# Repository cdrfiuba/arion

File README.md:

# Arión

Arión es un seguidor de líneas basado en la categoría Micromouse. Se caracteriza por ser tanto pequeño como liviano, y por estar siempre en búsqueda de innovaciones que le permitan tener mayor velocidad y mejor control, mediante diferentes mejoras de mecánica, electrónica y software. Nuestro objetivo es ganar las varias competencias de carreras que organiza la Liga Nacional de Robótica, mientras proporcionamos un diseño abierto y fácilmente replicable, para que cualquiera pueda hacer su propio robot y hacerle las modificaciones que potencien el estado de la robótica en nuestro país.

## Estado Actual

Un primer prototipo con varias adaptaciones obtuvo el tercer lugar en la Liga Nacional de Robótica de 2015. Actualmente estamos estandarizando estas adaptaciones para tener un diseño monolítico, tanto de mecánica y electrónica como de software.

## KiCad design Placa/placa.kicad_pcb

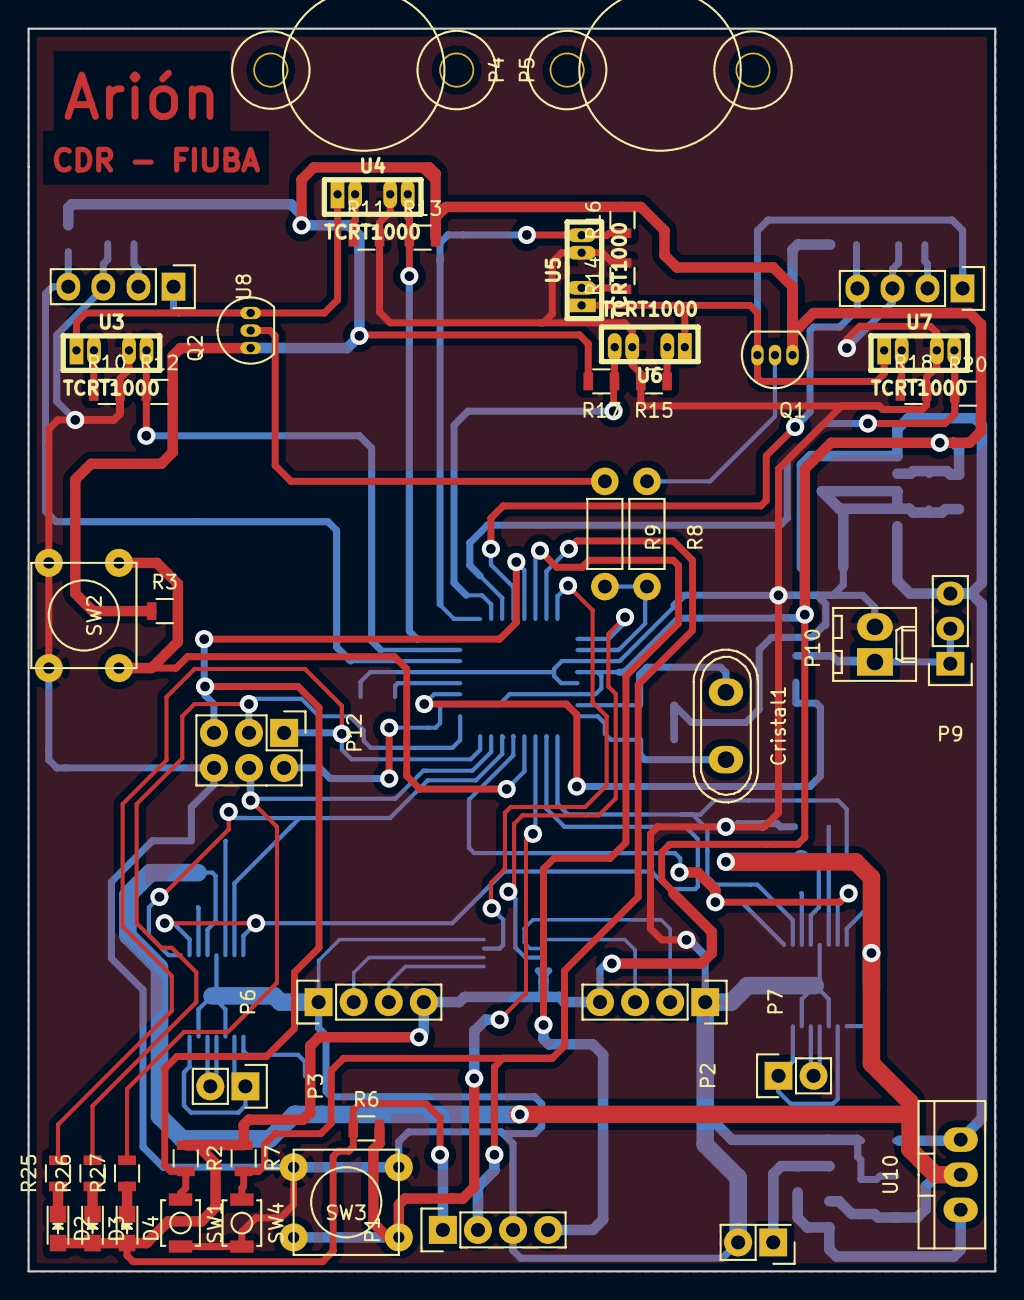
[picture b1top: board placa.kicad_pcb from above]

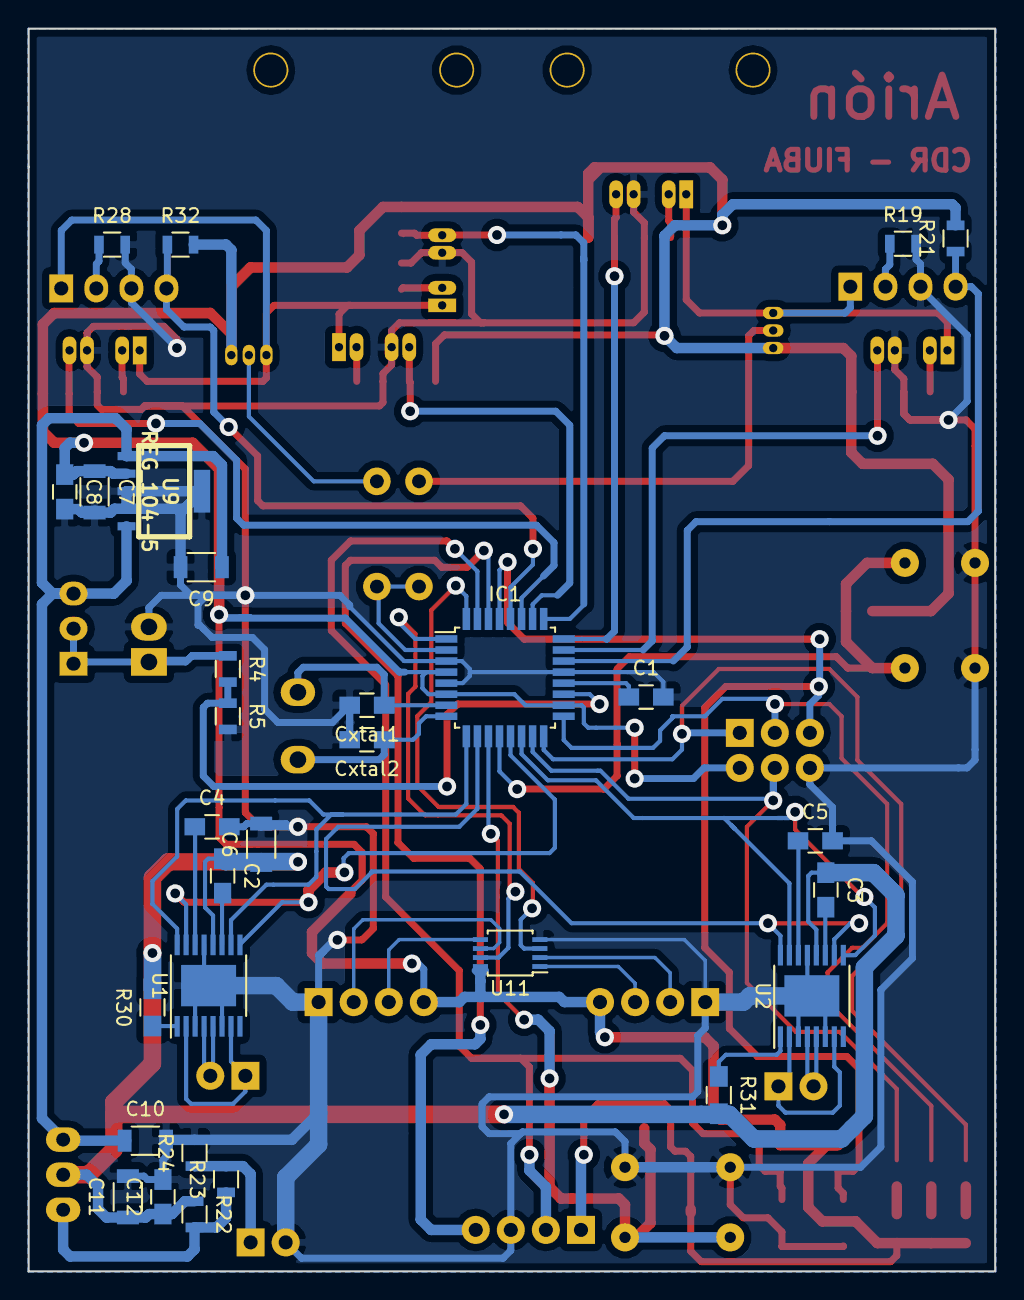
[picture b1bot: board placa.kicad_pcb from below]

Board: 2 copper layers, 70.0 x 90.0 mm, 78 parts (30 on the bottom side), 61 nets.

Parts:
C1: C; C_0805_HandSoldering
C2, C3: 0.01u; C_0805_HandSoldering
C4, C5: 2.2u; C_0805_HandSoldering
C6: 10uF; C_1206
C7, C9, C10, C11: 10u; C_1206
C8: 100n; C_0805_HandSoldering
C12: 0.1u; C_0805_HandSoldering
Cristal1: Crystal; Crystal_HC50-U_Vertical
Cxtal1, Cxtal2: 22p; C_0805_HandSoldering
D2, D3, D4: LED; LED_0805
IC1: ATMEGA328-A; TQFP-32_7x7mm_Pitch0.8mm
JP1: JUMPER; Pin_Header_Straight_2x01
P1, P6, P7: CONN_01X04; Pin_Header_Straight_1x04
P2, P3: CONN_01X02; Pin_Header_Straight_1x02
P4: BallCaster2; Pin_Header_Straight_1x02
P5: BallCaster1; Pin_Header_Straight_1x02
P9: CONN_01X03; Pin_Header_Straight_1x03
P10: CONN_01X02; Molex_KK-6410-02_02x2.54mm_Straight
P12: CONN_02X03; Pin_Header_Straight_2x03
Q1, Q2: BC548; TO-92_Inline_Narrow_Oval
R2, R3, R6, R7: 10k; R_0805
R4, R5, R12, R13, R16, R17, R20, R21, R32: 33k; R_0805
R8, R9: 2k2; Resistor_Horizontal_RM7mm
R10, R11, R14, R15, R18, R19, R28: 180; R_0805
R22: 120; R_0805
R23: 470; R_0805
R24: 270; R_0805
R25, R26, R27: 220; R_0805
R30, R31: 47k; R_0805_HandSoldering
SW1, SW4: SW_PUSH_SMALL; SW_SPST_B3U-1000P
SW2, SW3: SW_PUSH_SMALL
U1, U2: DVR8833; TSSOP-16_4.4x5mm_Pitch0.65mm
U3, U4, U5, U6, U7: TCRT1000
U8, U12: TCRT1000; Pin_Header_Straight_1x04
U9: REG_104-5; SOT223-5
U10: LM1084IT-ADJ/NOPB; TO-220_Neutral123_Vertical
U11: sn74lvc2g86; TSSOP-8_3x3mm_Pitch0.65mm

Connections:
+5V: C7.1, C8.1, D2.2, D3.2, D4.2, IC1.4, IC1.6, IC1.18, P1.1, P6.4, P7.4, P12.2, Q1.1, Q2.1, R2.1, R3.1, R6.1, R7.1, R12.2, R13.2, R16.2, R17.2, R20.2, R21.2, R32.2, U9.2, U11.8
+BATT: P9.1, P9.2, P10.1, R4.1
/Alimentacion/Vbat: C9.1, C10.1, P9.3, U9.1, U9.5, U10.3
/BatteryControl: IC1.19, R4.2, R5.1
/Boton1: IC1.12, R3.2, SW2.1
/Boton2: IC1.11, R6.2, SW3.1
/BotonExtra: IC1.31, P1.2, R7.2, SW4.1
/EncoderM1: IC1.1, U11.7
/EncoderM2: IC1.32, U11.3
/Led1: IC1.15, P12.4, R27.2
/Led2: IC1.16, P12.1, R25.2
/Led3: IC1.17, P12.3, R26.2
/Motores/M1IN1: IC1.13, U1.9, U1.15
/Motores/M1IN2: IC1.9, U1.10, U1.16
/Motores/M1OUT1: P2.1, U1.2, U1.7
/Motores/M1OUT2: P2.2, U1.4, U1.5
/Motores/M1VCP: C2.2, U1.11
/Motores/M1VINT: C4.1, U1.14
/Motores/M2IN1: IC1.14, U2.9, U2.15
/Motores/M2IN2: IC1.10, U2.10, U2.16
/Motores/M2OUT1: P3.1, U2.2, U2.7
/Motores/M2OUT2: P3.2, U2.4, U2.5
/Motores/M2VCP: C3.2, U2.11
/Motores/M2VINT: C5.1, U2.14
/RX: IC1.30, P1.4
/Reset: IC1.29, P12.5, R2.2, SW1.1
/Sensores/Habilitador: IC1.2, R8.2, R9.2
/Sensores/Sensor1: IC1.22, R21.1, U8.4
/Sensores/Sensor2: IC1.23, R12.1, U3.4
/Sensores/Sensor3: IC1.24, R13.1, U4.4
/Sensores/Sensor4: IC1.25, R16.1, U5.4
/Sensores/Sensor5: IC1.26, R17.1, U6.4
/Sensores/Sensor6: IC1.27, R20.1, U7.4
/Sensores/Sensor7: IC1.28, R32.1, U12.4
/Sensores/habilitado: Q1.3, U5.1, U6.1, U7.1, U12.1
/Sensores/habilitado2: Q2.3, U3.1, U4.1, U8.1
/XTAL1: Cristal1.1, Cxtal1.1, IC1.7
/XTAL2: Cristal1.2, Cxtal2.1, IC1.8
GND: C1.2, C4.2, C5.2, C6.2, C7.2, C8.2, C9.2, C10.2, C11.2, C12.2, Cxtal1.2, Cxtal2.2, IC1.3, IC1.5, IC1.21, JP1.2, P1.3, P6.1, P7.1, P10.2, P12.6, R5.2, R10.2, R11.2, R14.2, R15.2, R18.2, R19.2, R24.2, R28.2, SW1.2, SW2.2, SW3.2, SW4.2, U1.3, U1.6, U1.13, U2.3, U2.6, U2.13, U3.3, U4.3, U5.3, U6.3, U7.3, U8.3, U9.3, U9.4, U11.4, U12.3
unnamed: C1.1, IC1.20
unnamed: D2.1, R25.1
unnamed: D3.1, R26.1
unnamed: D4.1, R27.1
unnamed: JP1.1, R23.2, R24.1
unnamed: P6.2, U11.2
unnamed: P6.3, U11.1
unnamed: P7.2, U11.6
unnamed: P7.3, U11.5
unnamed: Q1.2, R8.1
unnamed: Q2.2, R9.1
unnamed: R10.1, U3.2
unnamed: R11.1, U4.2
unnamed: R14.1, U5.2
unnamed: R15.1, U6.2
unnamed: R18.1, U7.2
unnamed: R19.1, U8.2
unnamed: R22.2, R23.1, U10.1
unnamed: R28.1, U12.2
unnamed: R30.1, U1.1
unnamed: R31.1, U2.1
VPP: C2.1, C3.1, C6.1, C11.1, C12.1, R22.1, R30.2, R31.2, U1.12, U2.12, U10.2

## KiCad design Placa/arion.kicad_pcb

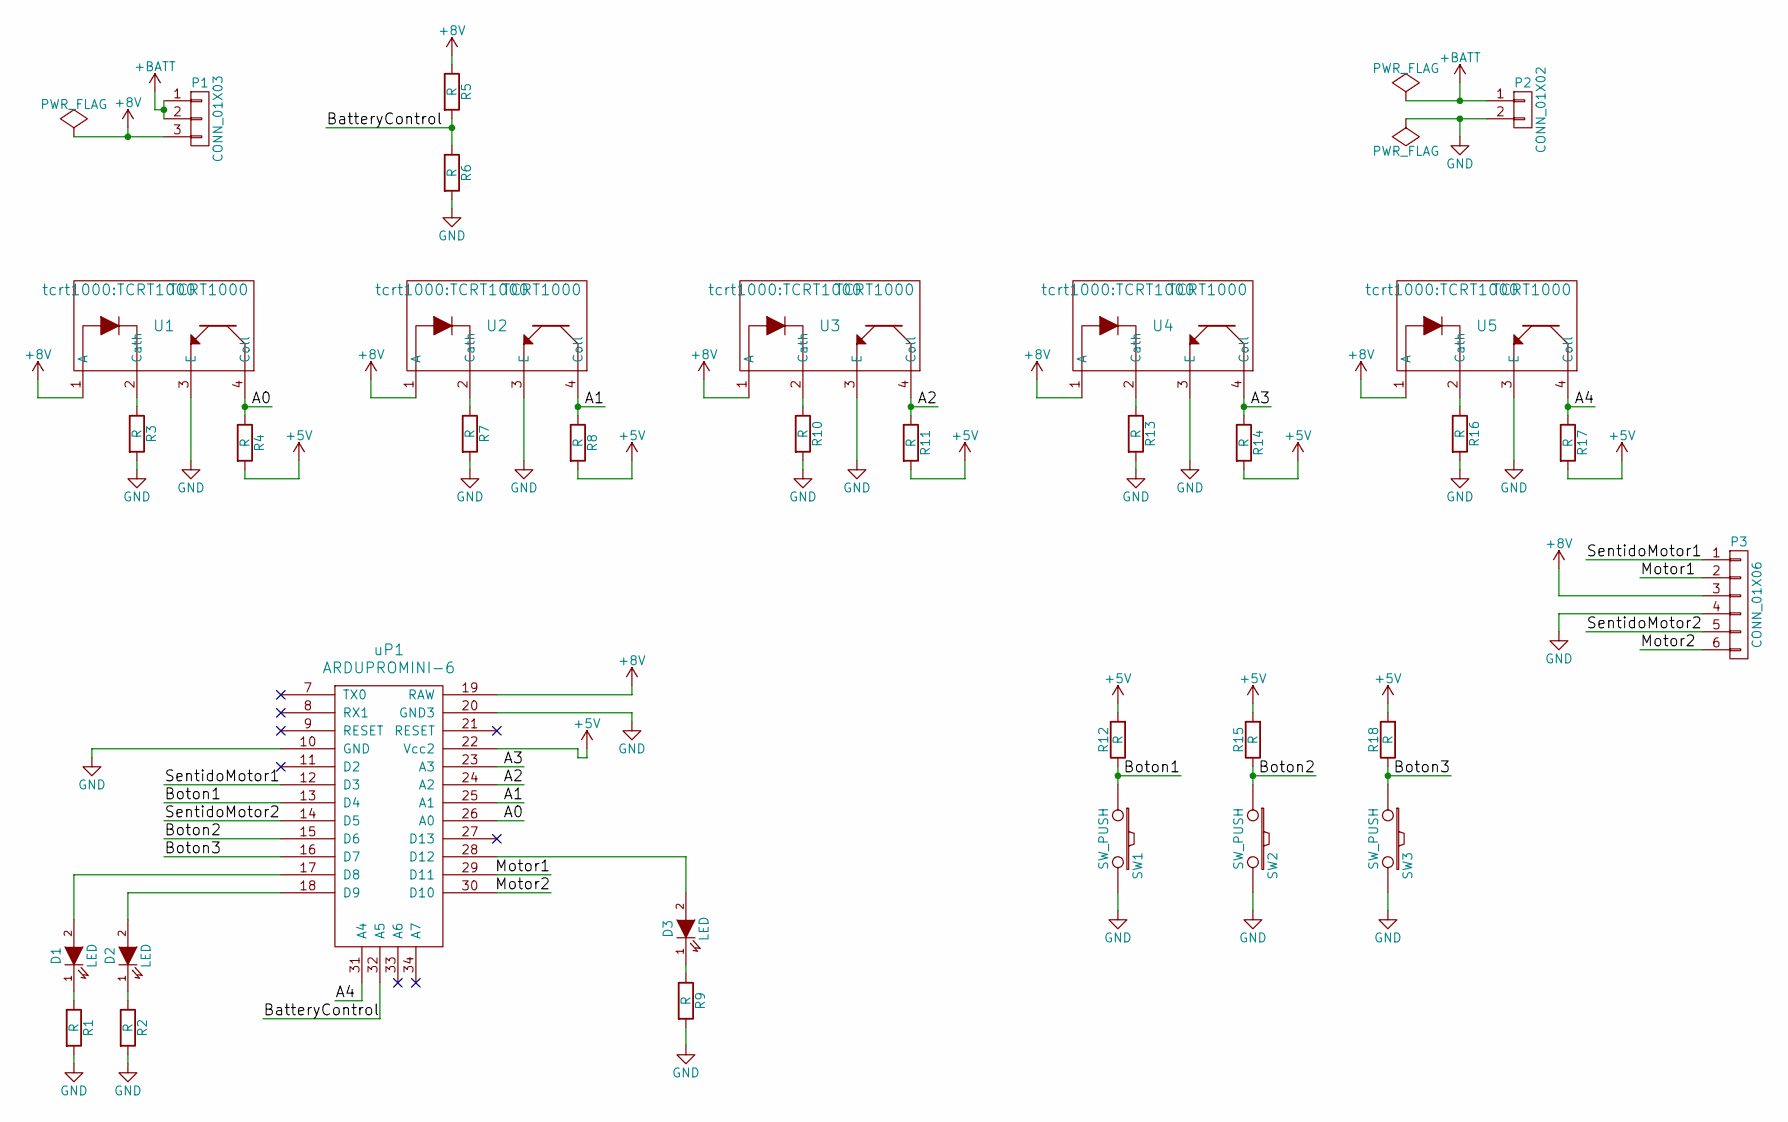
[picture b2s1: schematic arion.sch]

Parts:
D1, D2, D3: LED; R_0805_HandSoldering
P1: CONN_01X03; Pin_Header_Straight_1x03
P2: CONN_01X02; Pin_Header_Straight_1x02
P3: CONN_01X06; Pin_Header_Straight_1x06
R1, R2, R3, R4, R5, R6, R7, R8, R9, R10, R11, R12, R13, R14, R15, R16, R17, R18: R; R_0805_HandSoldering
SW1, SW2, SW3: SW_PUSH; SW_PUSH_SMALL
U1, U2, U3, U4, U5: TCRT1000
uP1: ARDUPROMINI-6; ArduProMini-6

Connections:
+5V: R4.2, R8.2, R11.2, R12.2, R14.2, R15.2, R17.2, R18.2, uP1.22 (Vcc2)
+8V: P1.3, P3.3, R5.1, U1.1 (A), U2.1 (A), U3.1 (A), U4.1 (A), U5.1 (A), uP1.19 (RAW)
+BATT: P1.1, P1.2, P2.1
/A0: R4.1, U1.4 (Coll), uP1.26 (A0)
/A1: R8.1, U2.4 (Coll), uP1.25 (A1)
/A2: R11.1, U3.4 (Coll), uP1.24 (A2)
/A3: R14.1, U4.4 (Coll), uP1.23 (A3)
/A4: R17.1, U5.4 (Coll), uP1.31 (A4)
/BatteryControl: R5.2, R6.1, uP1.32 (A5)
/Boton1: R12.1, SW1.1, uP1.13 (D4)
/Boton2: R15.1, SW2.1, uP1.15 (D6)
/Boton3: R18.1, SW3.1, uP1.16 (D7)
/Motor1: P3.2, uP1.29 (D11)
/Motor2: P3.6, uP1.30 (D10)
/SentidoMotor1: P3.1, uP1.12 (D3)
/SentidoMotor2: P3.5, uP1.14 (D5)
GND: P2.2, P3.4, R1.2, R2.2, R3.2, R6.2, R7.2, R9.2, R10.2, R13.2, R16.2, SW1.2, SW2.2, SW3.2, U1.3 (E), U2.3 (E), U3.3 (E), U4.3 (E), U5.3 (E), uP1.10 (GND), uP1.20 (GND3)
unnamed: D1.1 (K), R1.1
unnamed: D1.2 (A), uP1.17 (D8)
unnamed: D2.1 (K), R2.1
unnamed: D2.2 (A), uP1.18 (D9)
unnamed: D3.1 (K), R9.1
unnamed: D3.2 (A), uP1.28 (D12)
unnamed: R3.1, U1.2 (Cath)
unnamed: R7.1, U2.2 (Cath)
unnamed: R10.1, U3.2 (Cath)
unnamed: R13.1, U4.2 (Cath)
unnamed: R16.1, U5.2 (Cath)

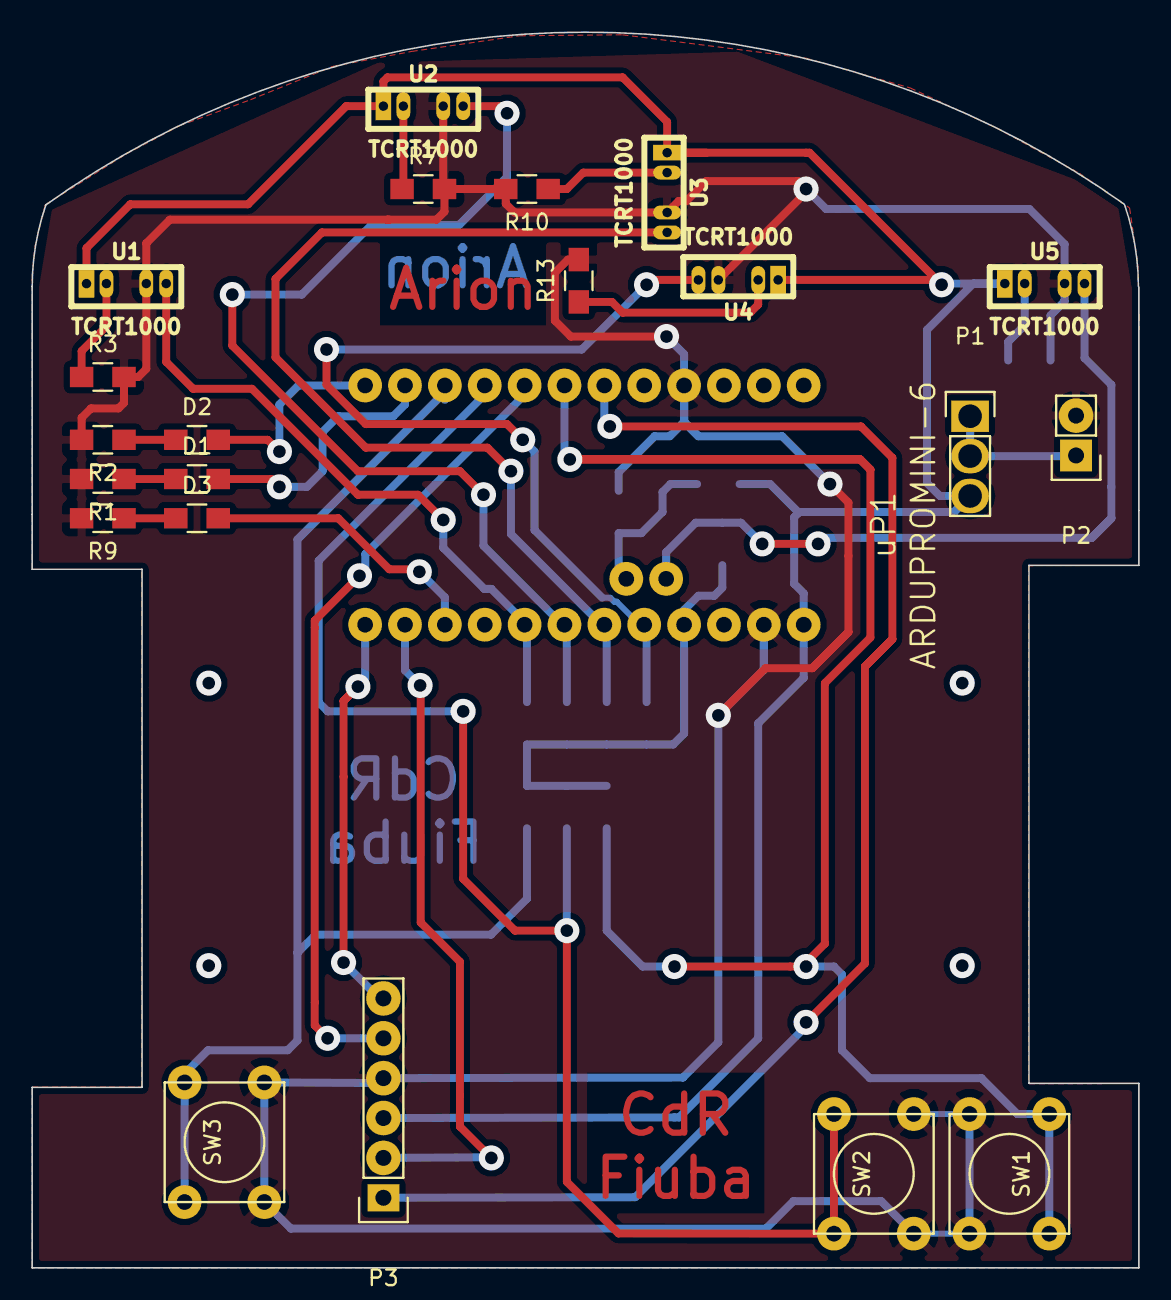
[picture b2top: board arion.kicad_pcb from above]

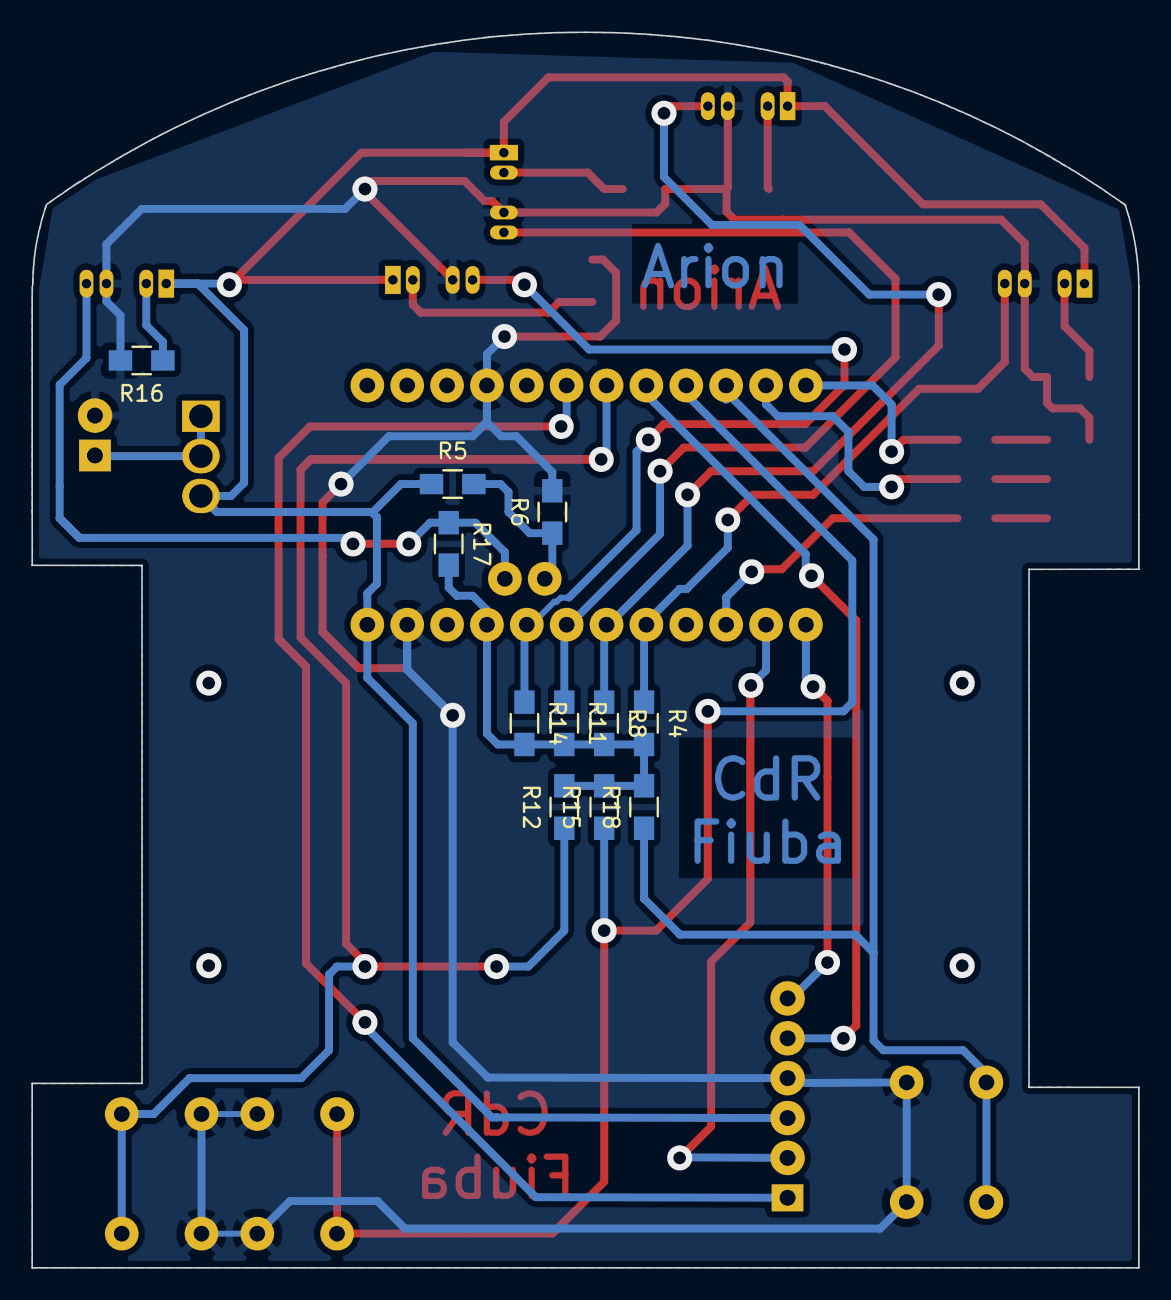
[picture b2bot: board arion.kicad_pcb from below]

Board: 2 copper layers, 70.5 x 78.7 mm, 33 parts (11 on the bottom side), 28 nets.

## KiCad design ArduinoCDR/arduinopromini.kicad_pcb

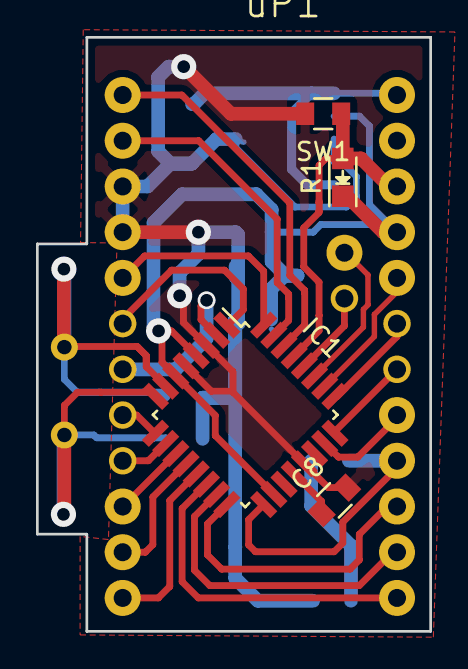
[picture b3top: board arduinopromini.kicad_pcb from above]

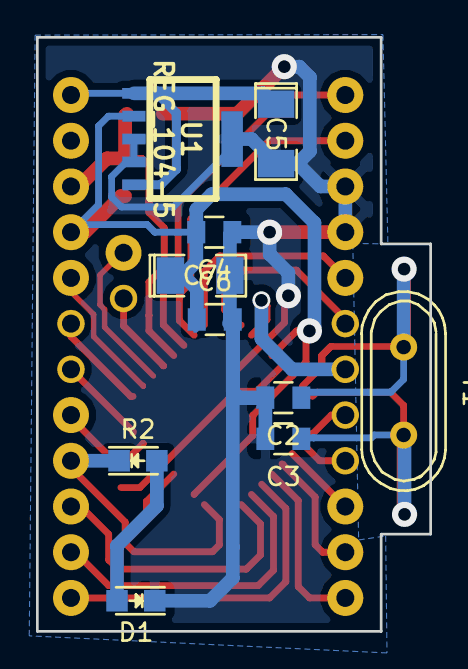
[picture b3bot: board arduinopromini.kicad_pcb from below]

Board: 2 copper layers, 21.8 x 33.0 mm, 15 parts (10 on the bottom side), 28 nets.

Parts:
C2, C3: 15 pF; C_0805
C4, C6, C8: 0.1 uF; C_0805
C5, C7: 10 uF; SMD-1206_Pol
D1: Verde; LED-0805
IC1: ATMEGA328-A; TQFP-32_7x7mm_Pitch0.8mm
R1: 10 k; LED-0805
R2: 330; LED-0805
SW1: SW_PUSH; C_0805
U1: REG_104-5; SOT223-5
Y1: 16 MHz; Crystal_HC49-U_Vertical
uP1: ARDUPROMINI-6; ArduProMinicdr2

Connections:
/xtal1: C2.1, IC1.7, Y1.1
/xtal2: C3.1, IC1.8, Y1.2
A0: IC1.23, uP1.26
A1: IC1.24, uP1.25
A2: IC1.25, uP1.24
A3: IC1.26, uP1.23
A4: IC1.27, uP1.31
A5: IC1.28, uP1.32
D2: IC1.32, uP1.11
D3: IC1.1, uP1.12
D4: IC1.2, uP1.13
D5: IC1.9, uP1.14
D6: IC1.10, uP1.15
D7: IC1.11, uP1.16
D8: IC1.12, uP1.17
D9: IC1.13, uP1.18
D10: IC1.14, uP1.30
GND: C2.2, C3.2, C4.1, C5.2, C6.2, C7.2, C8.2, D1.1, IC1.3, IC1.5, IC1.21, SW1.2, U1.3, U1.4, uP1.10
MISO: IC1.16, uP1.28
MOSI: IC1.15, uP1.29
unnamed: C8.1, IC1.20
unnamed: D1.2, R2.2
RST: IC1.29, R1.2, SW1.1, uP1.21
RXI: IC1.30, uP1.8
TX0: IC1.31, uP1.7
VCC: C4.2, C6.1, C7.1, IC1.4, IC1.6, IC1.18, R1.1, U1.2, uP1.22
raw: C5.1, U1.1, U1.5, uP1.19
sck: IC1.17, R2.1, uP1.27

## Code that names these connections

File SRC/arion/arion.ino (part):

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const int pwmMotorI = 10; // OC1B
const int sentidoMotorD = 5;
const int sentidoMotorI = 6;
const int led1 = 12;  // Led 1
const int led2 = 13;  // Led 2
const int led3 = 11;  // Led 3
const int boton1 = 8; // Boton1(pcb)   boton3 (code): Calibrar
const int boton2 = 7; // pin 1 arduino  - pin 31(avr)
const int boton3 = 7; // Boton2(pcb)   boton1 (code): Arrancar
const int sensor0 = A0; // sensor0 (code)   sensor2(pcb) izquierda  [izq]
const int sensor1 = A1; // cenIzq           sensor3(pcb)
const int sensor2 = A2; // cen              sensor4(pcb)
const int sensor3 = A3; // cenDer           sensor5(pcb)
const int sensor4 = A4; // der              sensor6(pcb)
const int batteryControl = A6; // 
const int sensorCurvaIzq = A7; //           sensor1(pcb)
const int sensorCurvaDer = A5; //           sensor7(pcb)
const int habilitador = 4; // PD4

// armado de array de sensores y arrays para calibración
const int cantidadDeSensores = 7;
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#define setBit(sfr, bit)   (_SFR_BYTE(sfr) |=  _BV(bit))
#define EEPROM_LENGTH 1024 // el ATmega328 tiene 1KB de EEPROM

#define led1On() digitalWrite(led1, LOW)
#define led2On() digitalWrite(led2, LOW)
#define led3On() digitalWrite(led3, LOW)
#define led1Off() digitalWrite(led1, HIGH)
#define led2Off() digitalWrite(led2, HIGH)
#define led3Off() digitalWrite(led3, HIGH)

#define detenerInterrupcionesADC() clearBit(ADCSRA, ADIE)
#define iniciarInterrupcionesADC() ADCSRA |= (1 << ADIE) | (1 << ADSC)
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  // como los sensores y el batteryControl se leen con AnalogRead,
  // no hace falta ponerlos como entrada
  //pinMode(sensor0, INPUT);
  //pinMode(sensor1, INPUT);
  //pinMode(sensor2, INPUT);
  //pinMode(sensor3, INPUT);
  //pinMode(sensor4, INPUT);
  //pinMode(batteryControl, INPUT);
  //pinMode(sensorCurvaIzq, INPUT);
  //pinMode(sensorCurvaDer, INPUT);

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  setBit(DIDR0, ADC1D);
  setBit(DIDR0, ADC0D);

  pinMode(led1, OUTPUT);
  pinMode(led2, OUTPUT);
  pinMode(led3, OUTPUT);
  pinMode(habilitador, OUTPUT);

  pinMode(boton1, INPUT);
  pinMode(boton2, INPUT);
  pinMode(boton3, INPUT);

  Serial.begin(SERIAL_BPS);

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
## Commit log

2015-07-02 Commit inicial de la placa
2015-07-04 Inicio del codigo de seguimineto de pista de Arión
2015-07-09 Terminado de adaptar PID de Tito, con algunas mejoras. Emprolijamiento general. Se acomodaron declaraciones, se quitaron números mágicos, y otros ajustes.
2015-07-13 Quitados los casteos explícitos a int32_t en el ciclo de PID.
2015-08-04 Cambios en el codigo. Base de tiempo en us
2015-08-04 Se cambiaron los errores que habia en la ultima version
2015-08-12 Mejorado debug. Invertidos sensores para usar con pista blanca. Agregadas conversiones a Long. Temporalmente deshabilitados I y D del PID. Intercambiados botones 1 y 3.
2015-08-15 Codigo modificado para hacer pruebas
2015-08-15 Empezada calibración, hechas pruebas y mejoras en relación al uso del tiempo en el PID
2015-08-15 Primer codigo que se mueve sobre la linea sin caerse
2015-08-15 Casi que con esto me presento
2015-08-15 Me presento de cabeza
2015-08-15 40 de velocidad y funciona!
2015-08-15 45, con 5 de continua
2015-08-15 ultimo comit con 45, vamos por mas
2015-08-15 cuatro vueltas a 75 +10
2015-08-17 Resultado de la competencia
2015-08-22 Agregado freno al cambiar de velocidad en ciclo PID. Mejorada velocidad del robot.
2015-08-22 Alcanzada la máxima velocidad de los motores
2015-08-22 Funciona la autocalibracion asistida
2015-09-22 Agrego archivos para el arduino pro mini propio
2015-09-23 branch 3PIDs
2015-09-24 Tiene velocidad de penalizacion. Tiene mejores parametros para rangoVelocidad 100. 5 vueltas 16 seg curva favorable
2015-09-26 23 segundos lasalle
2015-09-26 22.5 segundos lasalle
2015-09-26 22.7 segundos lasalle estable
2015-09-26 rama desarrollo
2015-09-26 Agregado sensor Curva, con modo Curva para ir lento/rapido. Los valores no estan perfectos.
2015-09-28 Codigo final con sensor incluido
2015-09-29 empezado clamp de sensores linea, nuevo modo afuera y valores de prueba
2015-10-01 Refactor. Movidas variables a loop(). Sacada calibración de setup(). Quitado parche sensorCurva.
2015-10-02 Agregado comentarios con los tiempos de procesamiento de los ciclos del programa
2015-10-03 prueba con sensor de curva en pista con rectas larga y curvas de 90 grados
2015-10-29 Optimizados sensado y calibración. Agregada velocidad por tramos. Serial activado siempre que no se esté en ciclo PID.
2015-11-03 Float PID
    Conversión a float de errores y calibración de sensores
2015-11-07 Tuneados valores de velocidad y PID.
2015-11-07 Tuneados parámetros, agregado tiempo máx velocidad para rectas
2015-11-21 Downgrade de estabilidad (lento y estable)
    Base de velocidad para lograr estabilidad en la pista de Bahía Blanca.
2015-11-21 Rápido y estable en ambos carriles: 16.09s en BB
2015-12-06 Agregado diseño para imprimir el molde de una rueda.
2015-12-07 Ajustes diseño molde. Agregado STL.
    Agregadas paredes para evitar rebalse, sacado código prototipo.
2016-01-09 Empezada limpieza de branch para versión 1.0
2016-01-23 Inicio de la version 2.0 de la placa
2016-02-20 Added files via upload
    Agrego archivo parametrizado para molde de silicona
2016-03-12 Agregados reguladores de tension en el PCB. Falta el puente H
2016-03-12 Empezado a parametrizar MoldeRuedaCaucho.
2016-03-17 MoldeRuedaCaucho: diseño de 30x10x5.
    Simplificado un poco el código, quitadas las paredcitas.
2016-03-17 MoldeRuedaCaucho: STLs de 30x15x5 y 30x10x5.
    Borrado viejo Molde.parametrizado.scad.
2016-04-02 Quitado código con error. Ahora compila.
2016-04-16 Versión estable.
2016-04-23 Agregados sub-esquemáticos. Avances en la placa.
2016-05-07 Avances sobre la placa.
2016-05-07 Creado README
2016-05-14 Más avances en placa. Ignorados archivos bak.
    Falta corregir algunas cosas en el esquemático, relacionado con los motores. El pcb está apenas empezado.
    Se ignoraron los archivos bak y cache de kicad.
2016-05-28 Placa: ajustes al sch del puente H.
2016-07-02 estan casi todas las cosas en su lugar, falta cambiar DVRs y regulador y rutear
2016-07-13 Cambio prematuro de etiquetas para saber qué cosas hay que cambiar.
2016-07-15 Agrego el componente para la compuerta xor
2016-07-15 Modificaciones a la placa
2016-07-16 se termino el esquematico y asociacion de componentes, falta acomodar y rutear PCB
2016-07-23 Está todo ruteado, falta engrozar pistas, chequear wiki y un chequeo general
2016-07-23 Actualizados parámetros con motores 10:1 HP.
2016-07-30 Agregado primer código para leer encoders.
2016-08-06 Ajustes a encoders.
2016-08-13 Se termino la placa, y se mando a fabricar.
2016-08-16 Primera prueba de medicion de tramos por encoder
2016-08-20 Agregado manejo de EEPROM para encoders.
2016-08-22 Corregidos typos, estilo, y editados comentarios.
    Cambiado cuánto cambia el mínimo de batería al apretar el botón.
2016-08-23 Avances con encoders.
    Implementado freno anticipado de curva, ajustados parámetros PID y
    velocidades, y agregado freno intenso durante principio de curva.
2016-08-25 Más parámetros.
2016-08-25 Agregado selector de carril para encoders.
2016-08-27 Movidos parámetros.
2016-08-30 Modicicacion de pines y debug para ver si andaba el nuevo PCB
2016-09-02 Confusión de nombres: migrado código de master.
2016-09-02 Confusión de nombres: migrado desde branch Brion.
2016-09-02 Renombrado proyecto de Arduino.
2016-09-03 Replanteados conceptos. Mejorada estabilidad.
2016-09-10 Parámetros. Movido chequeo de tensión de batería.
    Ahora se guarda el coeficiente de batería antes del arranque gradual de
    los motores.
2016-09-10 Params, pines, long a int. Calibración en EEPROM.
    Nuevos parámetros, puestos pines de leds y de botones, agregadas macros
    de leds (porque en este robot se prenden con LOW) y agregadas funciones
    para leer y escribir los mínimos y máximos de los sensores en EEPROM
    para almacenar el resultado de la calibración.
2016-09-13 Parámetros configurables por serie.
    Algunos parámetros ahora se pueden cambiar por serie, sin reprogramar.
    Las funciones de EEPROM todavía tenían alguna cosa long que debía ser
    int.
2016-09-17 Fix usarTiemposPorRecta.
2016-09-17 Restablecidos coeficientes sensores_linea.
2016-09-20 Ajustes Ayacucho.
2016-09-20 Agregado Sensor Curva Derecho. Sacados encoders.
    Se repitió el código del sensor curva izquierdo para el derecho, pero
    habría que poner un debounce o margen para que la lectura no tenga que
    ser simultánea en ambos sensores para cambiar de modo.
    Se deshabilitaron las interrupciones de los encoders.
2016-09-20 Fix sensores curva. Autocalibración. Botones.
    Ahora funciona el cambio de modo curva.
    La calibración ahora es automática, girando sobre el lugar.
    Intercambiados botones para arrancar con el del medio.
2016-09-24 Parámetros. Calibración. Freno post-curva.
    Rearmados parámetros.
    Calibración por EEPROM anda después de cambiar
    fuses.
    Agregado tiempo de freno al entrar en modo curva: rango velocidad pasa a
    ser 0 por el tiempo indicado por el nuevo parámetro.
2016-09-27 Parámetros con velocidad y estabilidad. Sin hacks.
2016-10-15 ADC asíncrono. Pruebas serie.
    Lectura de sensores por ADC asíncrono contínuo. Hacks para poder usar modo DEBUG sin que lleve tanto tiempo.
    Cambiado el modo en el que se espera a que se cumple el tiempoCicloReferencia.
2016-10-20 Primera version de Brion con encoders tiene modo de contar distancia para frenar antes de la marca de la curva
2016-10-21 Parámetros. Posible fix interrupciones ADC.
    Movidos, reajustados, y quitados varios parámetros.
    Separados arrays de sensores calibrados y sensores sin calibrar, para que ande igual en modo bloqueante como con interrupciones.
    Agregados y cambiados algunos comentarios.
2016-10-22 Pruebas prescaler Timer1.
    Probado cambiar frecuencia del Timer1 de los motores, en 4KHz, en 32KHz, y en 64Hz.
    Revertido clamp de sensores para modo afuera.
2016-10-22 Parámetros. Fix chequeo batería bloqueante.
    Estaban al revés los valores de los clamps de sensores línea.
    Agregadas macros para prender y apagar sólo las interrupciones de los
    ADC, para apagar las interrupciones globales, necesarias para el uso de
    delay().
    Probadas diferentes frecuencias de PWM.
2016-11-05 22/10 inclusion de la estimacion predictiva Linear Exponential Smoothing para la velocidad
2016-11-05 Quitado coast de motores. Debounce sensores curva.
    Cambiado modo PWM para que los motores no hagan coast, y poder controlar
    mejor los motores yendo para adelante.
    Permitido delay entre sensores curva para que no tengan que estar ambos
    prendidos para cambiar de modo curva.
2016-11-06 Implementacion de modo dual (3 PID y 1 PID+PWM). Cambio de escala de sensores y agregado de clamp
2016-12-16 Agrego cambios sugeridos en la wiki de github.
2017-03-18 Pruebas serie: ahora Serial anda a 2Mbps.
    Quitado input buffer a pines ADC mediante DIDR0.
